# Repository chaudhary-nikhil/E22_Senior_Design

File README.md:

# GoldenForm

ESP-IDF firmware and Python dashboard for **BNO055**-based swim stroke analysis: on-device logging, Wi‑Fi sync to the laptop/phone dashboard, 3D visualization, stroke metrics, and haptic coaching.

**PDP data path:** sessions are written to **SD** on the wearable and pulled by the dashboard over **Wi‑Fi** (`/process` / `data.json`). There is **no UART/serial pipeline** for production session transfer (USB is for `idf.py` flash/monitor only).

## Firmware

- **Target**: set in your tree (e.g. `esp32s3`); see `sdkconfig.defaults`.
- **Project name**: `GoldenForm` (`CMakeLists.txt` → `project(GoldenForm)`).
- **Main components**: `imu_bno055`, `stroke_detector`, `haptic`, `storage`, `wifi_server`, `protobuf`, `bus_i2c`, etc. (`main/CMakeLists.txt`).

```bash
source $HOME/esp/esp-idf/export.sh   # or your IDF env
cd /path/to/E22_Senior_Design
idf.py set-target <chip>
idf.py build flash monitor
```

## Dashboard (primary)

Serve the integrated app (handles `/process` sync from the wearable and static `integrated_session_viewer.html`):

```bash
cd dashboard
python3 wifi_session_processor.py
# Open the URL printed (default port 8844, or set `PORT` / `--port`)
```

Key files: `integrated_session_viewer.html`, `app.css`, `app.js`, `js/gf_*.js`, `wifi_session_processor.py` (uses `simple_imu_visualizer.StrokeProcessor` for session processing).

## Optional: USB session logger / legacy playback

`session_logger.py` + `session_visualizer.html` + `visualizer.js` remain for JSON sessions captured over serial; use the integrated dashboard above for the full GoldenForm flow (profile, devices, merge, ideal stroke).

## Data shape

Logged / synced samples include IMU, quaternion, calibration, stroke counts, and haptic fields as produced by the firmware and `StrokeProcessor` (see `dashboard/wifi_session_processor.py` and `dashboard/simple_imu_visualizer.py`).

## Requirements

- ESP-IDF (version aligned with this repo’s `esp-idf` or your install)
- Python 3 for the dashboard
- BNO055 + ESP32 as wired in project configuration

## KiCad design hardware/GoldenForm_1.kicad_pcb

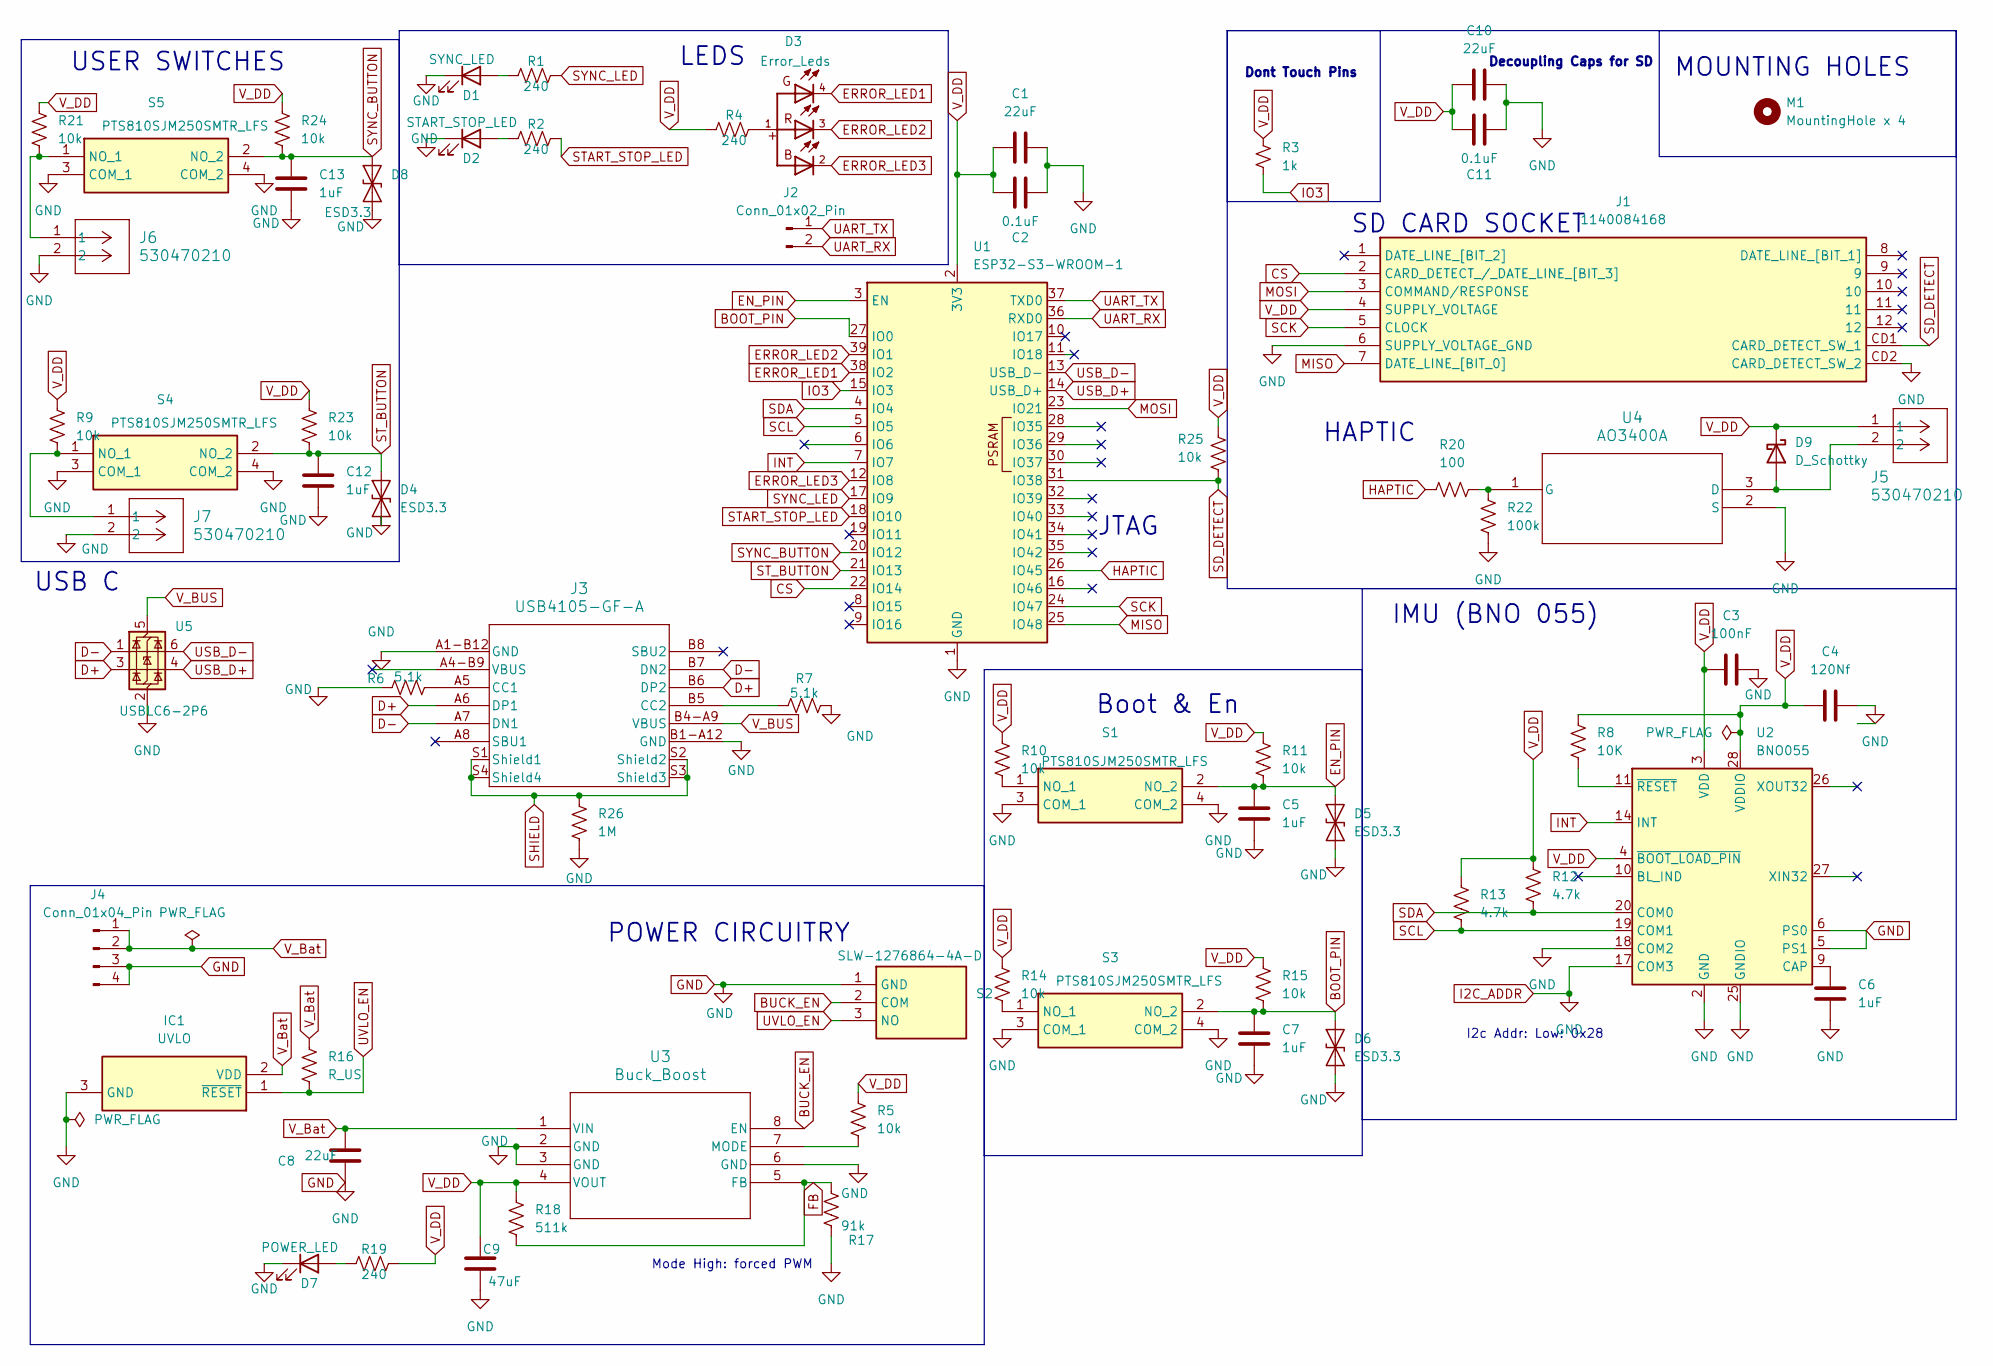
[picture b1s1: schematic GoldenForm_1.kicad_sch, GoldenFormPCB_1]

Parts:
C1, C10: 22uF; C_0805_2012Metric_Pad1.18x1.45mm_HandSolder
C2, C11: 0.1uF; C_0805_2012Metric_Pad1.18x1.45mm_HandSolder
C3: 100nF; C_0805_2012Metric_Pad1.18x1.45mm_HandSolder
C4: 120Nf; C_0805_2012Metric_Pad1.18x1.45mm_HandSolder
C5, C6, C7, C12, C13: 1uF; C_0805_2012Metric_Pad1.18x1.45mm_HandSolder
C8: 22uF; C_0603_1608Metric_Pad1.08x0.95mm_HandSolder
C9: 47uF; C_0603_1608Metric_Pad1.08x0.95mm_HandSolder
D1: SYNC_LED; LED_0805_2012Metric_Pad1.15x1.40mm_HandSolder
D2: START_STOP_LED; LED_0805_2012Metric_Pad1.15x1.40mm_HandSolder
D3: Error_Leds; WL-SFTW_3528_PLCC4; DigiKey_Part_Number 732-4998-1-ND
D4, D5, D6, D8: ESD3.3; D_0805_2012Metric_Pad1.15x1.40mm_HandSolder
D7: POWER_LED; LED_0805_2012Metric_Pad1.15x1.40mm_HandSolder
D9: D_Schottky; D_SOD-323_HandSoldering
IC1: UVLO; SOT95P237X112-3N; Mouser Part Number 595-TLV803EB33VDBZR
J1: 1140084168; Mouser Part Number 523-114-00841-68
J2: Conn_01x02_Pin; PinHeader_1x02_P2.54mm_Vertical
J3: USB4105-GF-A; USB4105_GCT
J4: Conn_01x04_Pin; PinHeader_1x04_P2.54mm_Vertical
J5, J6, J7: 530470210; CONN02_530470210_MOL
M1: MountingHole x 4; MountingHole_3.2mm_M3
R1, R2, R4, R19: 240; R_0805_2012Metric_Pad1.20x1.40mm_HandSolder
R3: 1k; R_0805_2012Metric_Pad1.20x1.40mm_HandSolder
R5, R9, R10, R11, R14, R15, R21, R23, R24, R25: 10k; R_0805_2012Metric_Pad1.20x1.40mm_HandSolder
R6, R7: 5.1k; R_0805_2012Metric_Pad1.20x1.40mm_HandSolder
R8: 10K; R_0805_2012Metric_Pad1.20x1.40mm_HandSolder
R12, R13: 4.7k; R_0805_2012Metric_Pad1.20x1.40mm_HandSolder
R16: R_US; R_0805_2012Metric_Pad1.20x1.40mm_HandSolder
R17: 91k; R_0805_2012Metric_Pad1.20x1.40mm_HandSolder
R18: 511k; R_0805_2012Metric_Pad1.20x1.40mm_HandSolder
R20: 100; R_0805_2012Metric_Pad1.20x1.40mm_HandSolder
R22: 100k; R_0805_2012Metric_Pad1.20x1.40mm_HandSolder
R26: 1M; R_0805_2012Metric_Pad1.20x1.40mm_HandSolder
S1, S3, S4, S5: PTS810SJM250SMTR_LFS; PTS810SJM250SMTRLFS; Mouser Part Number 611-PTS810SJM250SMTR
S2: SLW-1276864-4A-D; SLW12768644AD; Mouser Part Number 179-SLW-1276864-4A-D
U1: ESP32-S3-WROOM-1
U2: BNO055; LGA-28_5.2x3.8mm_P0.5mm
U3: Buck_Boost; MICROSIP8_SIU_TEX
U4: AO3400A; SOT-23-3L_AOS
U5: USBLC6-2P6; SOT-666

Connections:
BOOT_PIN: C7.1, D6.2 (A2), R15.2, S3.2 (NO_2), U1.27 (IO0)
BUCK_EN: S2.2 (COM), U3.8 (EN)
CS: J1.2 (CARD_DETECT_/_DATE_LINE_[BIT_3]), U1.22 (IO14)
D+: J3.A6 (DP1), J3.B6 (DP2), U5.3 (I/O2)
D-: J3.A7 (DN1), J3.B7 (DN2), U5.1 (I/O1)
EN_PIN: C5.1, D5.2 (A2), R11.2, S1.2 (NO_2), U1.3 (EN)
ERROR_LED1: D3.4, U1.38 (IO2)
ERROR_LED2: D3.3, U1.39 (IO1)
ERROR_LED3: D3.2, U1.12 (IO8)
FB: R17.1, R18.2, U3.5 (FB)
GND: C1.2, C2.2, C3.2, C4.1, C5.2, C6.2, C7.2, C8.2, C9.2, C10.2, C11.2, C12.2, C13.2, D1.1 (K), D2.1 (K), D4.1 (A1), D5.1 (A1), D6.1 (A1), D7.1 (K), D8.1 (A1), IC1.3 (GND), J1.6 (SUPPLY_VOLTAGE_GND), J1.CD2 (CARD_DETECT_SW_2), J3.A1-B12 (GND), J3.B1-A12 (GND), J4.3, J4.4, J6.2, J7.2, R6.1, R7.2, R17.2, R22.1, R26.2, S1.3 (COM_1), S1.4 (COM_2), S2.1 (GND), S3.3 (COM_1), S3.4 (COM_2), S4.3 (COM_1), S4.4 (COM_2), S5.3 (COM_1), S5.4 (COM_2), U1.1 (GND), U1.40 (GND), U1.41 (GND), U2.2 (GND), U2.5 (PS1), U2.6 (PS0), U2.17 (COM3), U2.18 (COM2), U2.25 (GNDIO), U3.2 (GND), U3.3 (GND), U3.6 (GND), U4.2 (S), U5.2 (GND)
HAPTIC: R20.1, U1.11 (IO18), U1.26 (IO45)
INT: U1.7 (IO7), U2.14 (INT)
IO3: R3.2, U1.15 (IO3)
IO15: U1.8 (IO15)
IO16: U1.9 (IO16)
IO17: U1.10 (IO17)
MISO: J1.7 (DATE_LINE_[BIT_0]), U1.25 (IO48)
MOSI: J1.3 (COMMAND/RESPONSE), U1.23 (IO21)
unnamed: D1.2 (A), R1.1
unnamed: D2.2 (A), R2.1
unnamed: D3.1, R4.2
unnamed: D7.2 (A), R19.1
unnamed: D9.2 (A), J5.2, U4.3 (D)
unnamed: J3.A5 (CC1), R6.2
unnamed: J3.B5 (CC2), R7.1
unnamed: R10.2, S1.1 (NO_1)
unnamed: R14.2, S3.1 (NO_1)
unnamed: J7.1, R9.2, S4.1 (NO_1)
unnamed: J6.1, R21.2, S5.1 (NO_1)
unnamed: C6.1, U2.9 (CAP)
unnamed: R8.2, U2.11 (~RESET)
unnamed: R5.2, U3.7 (MODE)
unnamed: R20.2, R22.2, U4.1 (G)
SCK: J1.5 (CLOCK), U1.24 (IO47)
SCL: R13.2, U1.5 (IO5), U2.19 (COM1)
SDA: R12.2, U1.4 (IO4), U2.20 (COM0)
SD_DETECT: J1.CD1 (CARD_DETECT_SW_1), R25.2, U1.31 (IO38)
SHIELD: J3.S1 (Shield1), J3.S2 (Shield2), J3.S3 (Shield3), J3.S4 (Shield4), R26.1
START_STOP_LED: R2.2, U1.18 (IO10)
ST_BUTTON: C12.1, D4.2 (A2), R23.2, S4.2 (NO_2), U1.21 (IO13)
SYNC_BUTTON: C13.1, D8.2 (A2), R24.2, S5.2 (NO_2), U1.20 (IO12)
SYNC_LED: R1.2, U1.17 (IO9)
UART_RX: J2.2, U1.36 (RXD0)
UART_TX: J2.1, U1.37 (TXD0)
USB_D+: U1.14 (USB_D+), U5.4 (I/O2)
USB_D-: U1.13 (USB_D-), U5.6 (I/O1)
UVLO_EN: IC1.1 (~RESET), R16.2, S2.3 (NO)
V_BUS: J3.B4-A9 (VBUS), U5.5 (VBUS)
V_Bat: C8.1, IC1.2 (VDD), J4.1, J4.2, R16.1, U3.1 (VIN)
V_DD: C1.1, C2.1, C3.1, C4.2, C9.1, C10.1, C11.1, D9.1 (K), J1.4 (SUPPLY_VOLTAGE), J5.1, R3.1, R4.1, R5.1, R8.1, R9.1, R10.1, R11.1, R12.1, R13.1, R14.1, R15.1, R18.1, R19.2, R21.1, R23.1, R24.1, R25.1, U1.2 (3V3), U2.3 (VDD), U2.4 (~BOOT_LOAD_PIN), U2.28 (VDDIO), U3.4 (VOUT)

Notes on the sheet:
LEDS
SD CARD SOCKET
POWER CIRCUITRY
Mode High: forced PWM
USB C
IMU (BNO 055)
USER SWITCHES
Decoupling Caps for SD
Dont Touch Pins
HAPTIC
JTAG
Boot & En
I2c Addr: Low: 0x28
MOUNTING HOLES

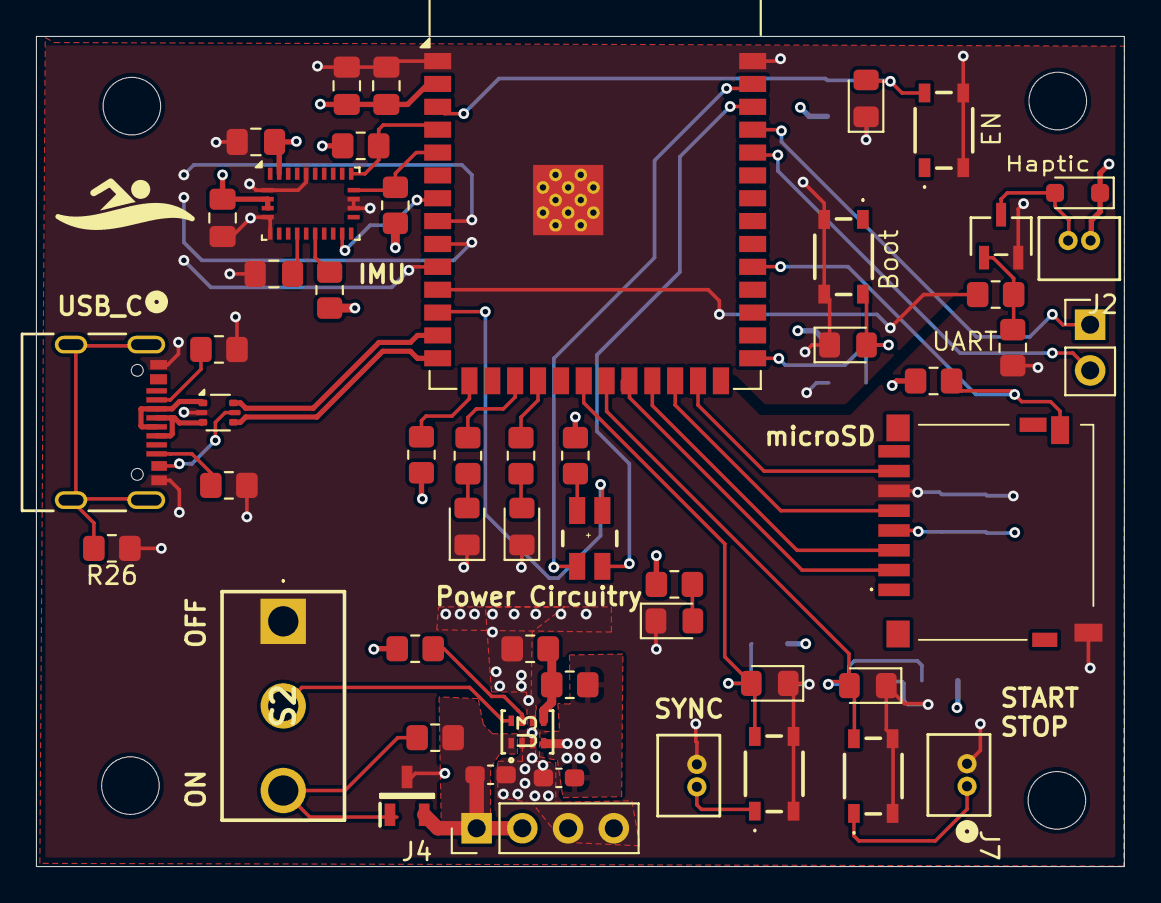
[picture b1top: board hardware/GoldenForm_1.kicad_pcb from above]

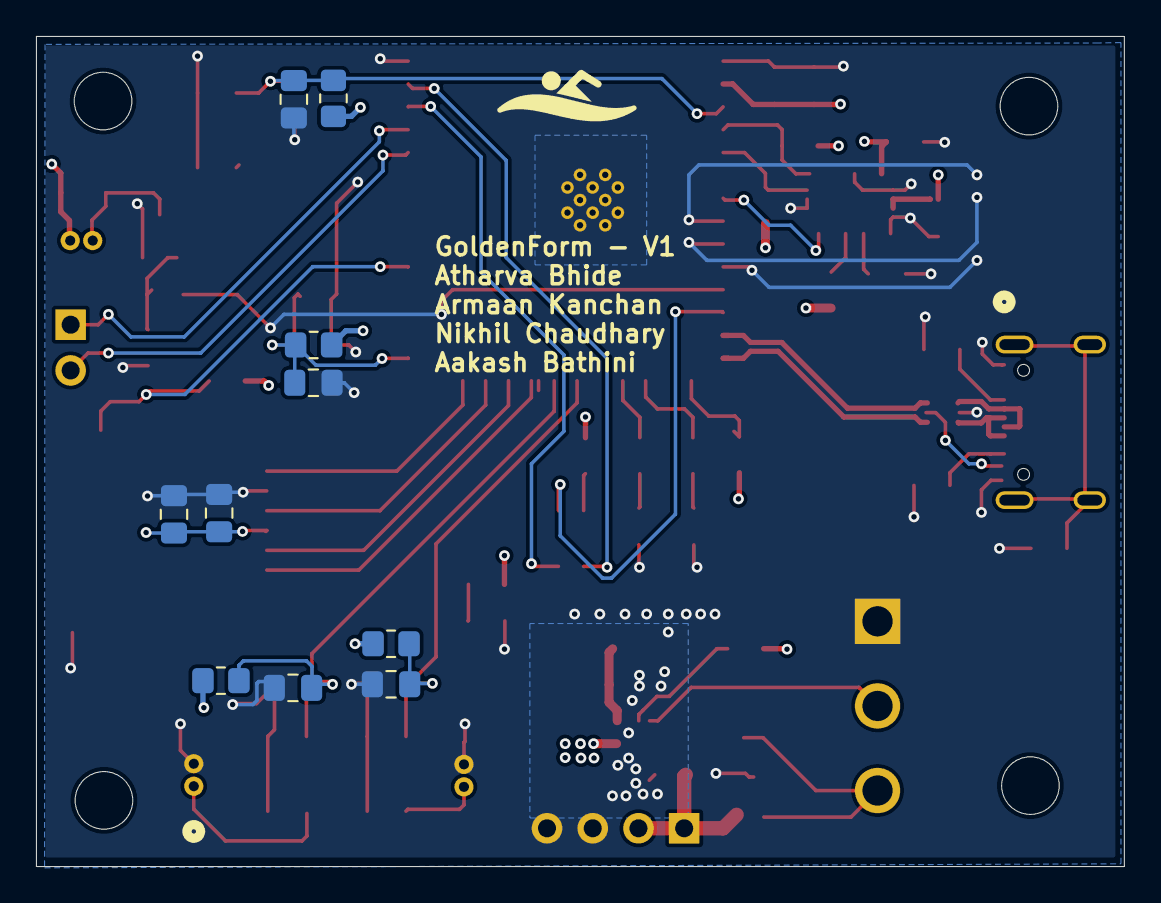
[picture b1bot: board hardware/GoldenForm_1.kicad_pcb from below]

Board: 4 copper layers, 60.4 x 46.1 mm, 62 parts (10 on the bottom side), 46 nets.

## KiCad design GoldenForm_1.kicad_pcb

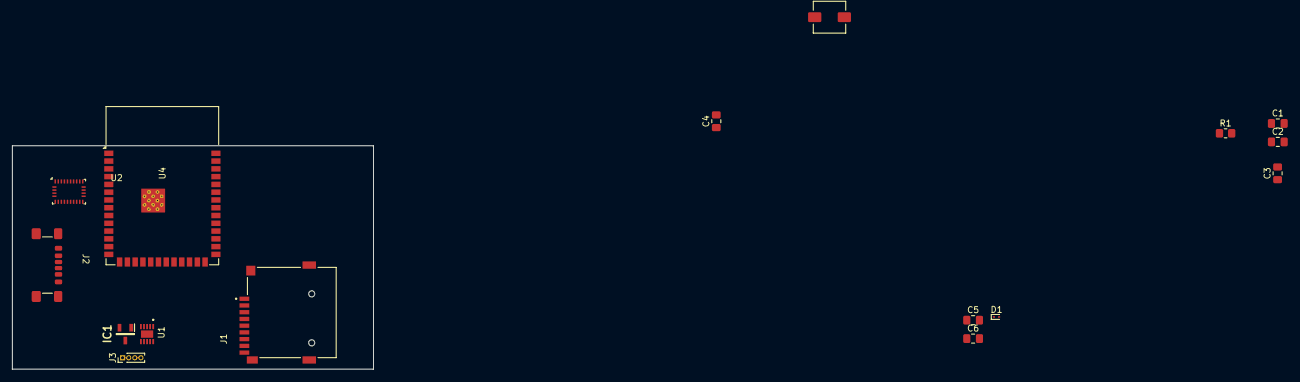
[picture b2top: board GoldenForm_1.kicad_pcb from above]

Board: 2 copper layers, 59.0 x 36.5 mm, 16 parts (0 on the bottom side), 17 nets.

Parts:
C1: 20uF; C_0805_2012Metric_Pad1.18x1.45mm_HandSolder
C2, C4: 10uF; C_0805_2012Metric_Pad1.18x1.45mm_HandSolder
C3: C; C_0805_2012Metric_Pad1.18x1.45mm_HandSolder
C5: 1uF; C_0805_2012Metric_Pad1.18x1.45mm_HandSolder
C6: 120Nf; C_0805_2012Metric_Pad1.18x1.45mm_HandSolder
D1: ESD3.3; D_SOD-923
IC1: UVLO; SOT95P237X112-3N
J1: SD_Socket; CUI_MSD-4-A
J2: USB_C_Receptacle_USB2.0_14P; USB_C_Receptacle_GCT_USB4135-GF-A_6P_TopMnt_Horizontal
J3: Conn_01x04_Pin; PinHeader_1x04_P1.00mm_Vertical
L2: SRP5030T-2R2M; INDM5752X300N
R1: R_US; R_0805_2012Metric_Pad1.20x1.40mm_HandSolder
U1: Buck_Boost; SON50P250X250X80-11N
U2: BNO055; LGA-28_5.2x3.8mm_P0.5mm
U4: ESP32-S3-WROOM-1

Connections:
CS: J1.2 (CD/DAT3), U4.25 (IO48)
GND: C1.1, C2.2, C3.2, C4.2, C5.2, D1.1 (A1), IC1.3 (GND), J1.6 (VSS), J2.A12 (GND), J2.B12 (GND), J2.S1 (SHIELD), J3.3, J3.4, U1.3 (GND), U1.9 (GND__1), U1.11 (EXP), U2.2 (GND), U4.1 (GND), U4.40 (GND), U4.41 (GND)
GNDIO: C6.1, U2.5 (PS1), U2.6 (PS0), U2.18 (COM2), U2.25 (GNDIO)
JTAG: U4.32 (IO39), U4.33 (IO40), U4.34 (IO41), U4.35 (IO42)
MISO: J1.7 (DAT0), U4.22 (IO14)
MOSI: J1.3 (CMD), U4.24 (IO47)
unnamed: D1.2 (A2), U4.3 (EN)
unnamed: IC1.1 (~RESET), R1.2, U1.6 (EN)
unnamed: L2.1, U1.4 (LX1)
unnamed: L2.2, U1.2 (LX2)
unnamed: C5.1, U2.9 (CAP)
unnamed: C6.2, U2.28 (VDDIO)
PSRAM: U4.28 (IO35), U4.29 (IO36), U4.30 (IO37)
SCK: J1.5 (CLK), U4.23 (IO21)
VBUS: J2.A9 (VBUS), J2.B9 (VBUS)
V_Bat: C2.1, IC1.2 (VDD), J3.1, J3.2, R1.1, U1.5 (VIN), U1.8 (VINA)
V_DD: C1.2, C3.1, C4.1, J1.4 (VDD), U1.1 (VOUT), U1.10 (FB), U2.3 (VDD), U4.2 (3V3)

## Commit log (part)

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2025-09-30 Add project title and description to README
2025-10-01 ESP32 Wroom boilerplate
2025-10-06 cleanup
2025-10-06 Clean up codebase - remove unused components and files
    - Remove unused live_imu_visualizer.py and live_imu_3d.html
    - Remove websocket_simple component completely
    - Clean up main CMakeLists.txt comments
    - Keep only essential components: bus_i2c, imu_mpu6050, serial_stream
    - Keep only working visualization: simple_imu_visualizer.py and simple_imu_3d.html
    - System builds successfully and Python visualizer works
2025-10-06 Reorganize project structure and add comprehensive documentation
    - Create docs/ folder with comprehensive README.md
    - Move Python visualizer to scripts/ folder for better organization
    - Remove unused files (main.c, Kconfig.projbuild)
    - Update README with complete setup and usage instructions
    - Clean project structure: docs/, scripts/, components/, main/
    - System builds successfully and Python visualizer works
2025-10-08 added new functionality for visual charts of the acceleration and angular velocity
2025-10-08 Create README.md for FormSync Firmware Template
    Added initial README with project structure and build instructions.
2025-10-13 testing sd card code
2025-10-17 added new functionality for visual charts (#5)
    * added new functionality for visual charts of the acceleration and angular velocity
    * adding codeowners file
2025-10-20 added folder for bno 9 axis imu
2025-10-21 Fix ESP32 connection messages and add missing endpoints
    - Remove excessive 'Connected to ESP32' messages (only show once)
    - Add visualizer.js endpoint handler to fix 404 error
    - Add missing /session_status endpoint
    - Improve error handling for serial reconnections
2025-10-21 Add sessions directory and dynamic orientation analysis
    - Create dashboard/sessions/ directory for organized JSON storage
    - Update all file paths to use sessions/ directory
    - Add dynamic orientation analysis based on acceleration data
    - Fix emergency save logic to only save when actively logging
    - Update README with sessions directory documentation
2025-10-21 Create merge-safe README documenting both MPU6050 and BNO055 systems
    - Documents both MPU6050 (live visualization) and BNO055 (session logging) systems
    - Preserves main branch structure and build instructions
    - Adds comprehensive BNO055 swim analysis documentation
    - Ensures clean merge with main branch
2025-10-21 Fix critical issues identified by Copilot AI
    - Fix undefined data_lock variable in session_logger.py
    - Fix BNO055 accelerometer unit conversion (mg/LSB to m/s²)
    - Fix BNO055 gyroscope unit conversion (dps to rad/s)
    - Use CONFIG_FORMSYNC_SAMPLE_HZ instead of hardcoded sampling period
    - Improve playback timing accuracy with session_time-based delays
    All fixes ensure proper sensor data accuracy and system reliability.
2025-10-21 Fix timing and session management issues identified by Copilot
    - Use monotonic time for session timestamps (prevents NTP/clock drift issues)
    - Fix BNO055 session start time to reset between sessions
    - Replace hardcoded playback delay bounds with dynamic calculation
    - Calculate bounds based on actual sample rate characteristics
    - Ensure accurate timing regardless of system clock changes
    All timing issues resolved for reliable session logging and playback.
2025-10-21 Remove unused function declaration from BNO055 header
    - Remove bno055_reset_session_timestamp declaration
    - Function was not implemented, only declaration existed
    - Clean up header file
2025-10-21 added the new way to add csv packets not verified
2025-10-23 Redid flow: ESP32 independent logging with WiFi data transfer
    - Removed BLE, serial communication, and unnecessary components
    - Implemented ESP32-controlled logging with BOOT button toggle
    - Added WiFi server for data transfer to dashboard
    - Updated dashboard to handle WiFi-based session data
    - Cleaned up codebase and removed duplicate functionality
    - Fixed import errors and consolidated session management
2025-10-24 sessions now being added, able to send from esp over wifi server, do GET /session_data on python end and receive
2025-10-27 added 9 axis funcs for storage
2025-10-29 sessions now being added, able to send from esp over wifi server, do GET /session_data on python end and receive (#13)
2025-11-03 trying to send GPS via UART
2025-11-07 added test main file that generates data
2025-11-10 testing sd card + wifi func together
2025-11-11 Update WiFi implementation and dashboard components
2025-11-11 Add trail visualization to show movement path over time
2025-11-13 added Lia read
2025-11-13 just imu
2025-11-14 working visuals
2025-11-19 comment for psedu logic
2025-11-20 Potential IMU fixes do not merge
2026-01-19 Add professional swimming stroke visualization and analysis
    - Physics-based stroke detection: detects water entry via downward motion
    followed by deceleration spike (research-backed from SwimBIT papers)
    - Phase-colored trails: cyan=recovery, yellow=transition, orange/red=power phase
    - Stroke analysis panel: duration, path length, stroke rate, consistency score
    - Comparison view: overlay up to 10 past strokes for technique comparison
    - Water reference plane: optional grid showing water surface orientation
2026-01-19 Atharva integral try (#17)
    * added Lia read
    * imu visualizer with calibration, added some integration logic too, issues with html
    * working visuals
    * Configure ESP-IDF for VS Code and make paths portable
    - Add VS Code settings for ESP-IDF extension
    - Update CMakeLists.txt to use portable paths (HOME instead of hardcoded)
2026-01-21 Nikhil/feature/sd card integration (#18)
    * added Lia read
    * imu visualizer with calibration, added some integration logic too, issues with html
    * working visuals
    * Configure ESP-IDF for VS Code and make paths portable
    - Add VS Code settings for ESP-IDF extension
    - Update CMakeLists.txt to use portable paths (HOME instead of hardcoded)
2026-01-23 PCB stuff - not fully done
2026-01-23 Fix LED control, PSRAM sync, and add test data generator
    - Fixed LED blink task with proper task handle and increased stack (2048)
    - Added led_blink_start() and led_blink_stop_and_wait() for clean task control
    - Added startup LED test (2 blinks) to verify GPIO2 is working
    - Enabled PSRAM (8MB Octal mode) for sync buffer allocation
    - Added test data generator when no SD card data available
    - Fixed race condition when transitioning from SYNCING to IDLE
2026-01-23 Improve serial monitor output for testing without LED
    - Removed LED startup test (module may not have LED)
    - Added helpful serial message about watching monitor
    - Fixed status counter to reset when not idle
    - Code ready for SD card + WiFi transfer testing
2026-01-24 WIP SD card reads wireless transfer flow
2026-01-26 Fix protobuf decode stack overflow and address PR comments
    - Fix: Allocate formsync_ImuSampleBatch on heap in protobuf_decode_batch (was causing stack overflow)
    - Fix: Use malloc/free consistently for protobuf read buffers (simplified from heap_caps)
    - Clarify: Updated comments to use 'protobuf' instead of 'protobuf-like'
    - Document: Added comments explaining FLUSH_INTERVAL_MS vs FILE_ROLLOVER_MS difference
    - Verify: Enhanced I2C timeout logging with calculated values and verification
    - Note: Test data generation removed (was in wifi_server_start_sync)
2026-01-28 WIP fixing sample count
2026-01-28 changing the SD reader to Adafruit MicroSD SPI
2026-01-28 cleanup again
2026-01-28 Update sdkconfig
    Update components/bus_i2c/bus_i2c.c
2026-01-29 conflict resolved don't merge to main yet
2026-01-30 now check
2026-01-31 send saved data in sd card through wifi from the esp32 to the server (#20)
    * Add ESP32-S3 support with WiFi server integration
    - Updated firmware for ESP32-S3-WROOM-1 based on schematic
    - Integrated WiFi server component from atharva_wifi_check branch
    - Implemented 4-state machine (IDLE, LOGGING, STOPPED, SYNCING) controlled by BOOT button
    - Added binary protobuf-like storage format for SD card
    - Configured I2C pins for BNO055 (SDA=GPIO4, SCL=GPIO5, ADDR=GPIO6)
2026-01-31 more cleanup and added 9600 folder to gitignore
2026-02-02 added mounting holes to sch
2026-02-03 some new changes
2026-02-03 added Symbols to table
2026-02-04 added LED logic (#23)
2026-02-04 Fixing ERC Check Errors/Warnings (#22)
    * some new changes
    * more changes for ERC cleanup
    * added Symbols to table
    * wip
    * WIP
    * 3 ERC warnings now
2026-02-04 oops renamed to LED_2
2026-02-05 added new sd card socket, esd protection for boot and en, uart debug
2026-02-07 placed the components on the PCB
2026-02-08 started routing. added classes and stuff
2026-02-08 need to sort DRCs
2026-02-10 integration wifi ivusal
2026-02-12 WIP ESD protection for USB receptacle
2026-02-13 changed holes in ground pad for esp32 micro
2026-02-15 added caps for vdd sd, added esd for usbc, fixed i2c addr from bno
2026-02-17 added silkscreen, logo, etc.
2026-02-26 added shield res, and ext button headers
2026-03-05 final PCB
2026-03-06 Revert generated sdkconfig churn
    Drop the tracked sdkconfig noise from this branch while keeping the intentional sdkconfig.defaults change so the eventual merge back to main stays easier to review.
    Made-with: Cursor
2026-03-06 hand in visualizer
2026-03-07 Implement DTW machine learning for stroke classification
2026-03-07 fix geenrate mock
2026-03-07 charts now show in app for session data
2026-03-07 ported over 3d visualization to the new dashboard
2026-03-11 changes to make modular
2026-03-26 audit and stretch
2026-03-26 haptic working well
2026-03-28 merge
2026-04-02 Viz: LIA-first 3D defaults, drift-tuned integration, cleaner scene
    StrokeProcessor: vector deadzone when accel+gyro fusion >=2; quiet-sample
    velocity bleed; comments clarify Wi‑Fi uses same world LIA physics as legacy.
    App: default path mode position; smaller hand scale; softer water/fog/trail;
    ghost ideal as subtle solid (off by default); swimmer silhouette off by default;
    checkboxes for ideal overlay and swimmer ref; ideal overlay respects checkbox.
    Firmware: document IMU sample path parity with dashboard integration.
2026-04-09 Update .gitignore to exclude environment files; modify sdkconfig for device ID and enable multi-device support; enhance bno055.c with new operation mode handling and calibration logging; update dashb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
2026-04-09 added replay button
2026-04-09 Enhance stroke detection and dashboard features: Adjust haptic thresholds and warmup logic in stroke detector; update dashboard styles for improved user experience; add haptic feedback metrics to ses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
2026-04-13 fixed statvfs issues
2026-04-13 sd card demo stuff
2026-04-14 Update sdkconfig for device ID and role; enhance error logging in app_main for SD card and IMU read errors; add IDF setup path in VSCode settings.
2026-04-14 cv new files
2026-04-17 IMU viz + StrokeProcessor: 0401fbde alignment, UX, firmware polish
    - StrokeProcessor: motion-gate segment resets (live+batch), quiet streak to
    reduce gate flutter; cal-fail and /reset clear gate state; land-demo stroke
    detection tightened; batch replay notes for GF_REPLAY_INTEGRATION.
    - Dashboard: per-stroke origin (catch/pull), prefer stroke_count over fw strokes;
    side-view PCA sign fix; lockable side camera + shared sagittal transform;
    auto-scale stroke + camera frame; tracking HUD; default position scale.
2026-04-20 BNO055 FIX POTENTIALLY
2026-04-20 hardware reset too
2026-04-21 tweaked some things, looks better now
2026-04-21 Update GPIO configuration for goldenform button and remove turn count from IMU and protobuf structures. Adjust stroke detection logic to eliminate turn detection and enhance haptic feedback settings 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
2026-04-21 added dummy flow in main
2026-04-21 visualizer fix should be patched now
